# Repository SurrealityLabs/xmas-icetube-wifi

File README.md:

# xmas-icetube-wifi
Wifi adapter for the xmas-icetube clock PCB

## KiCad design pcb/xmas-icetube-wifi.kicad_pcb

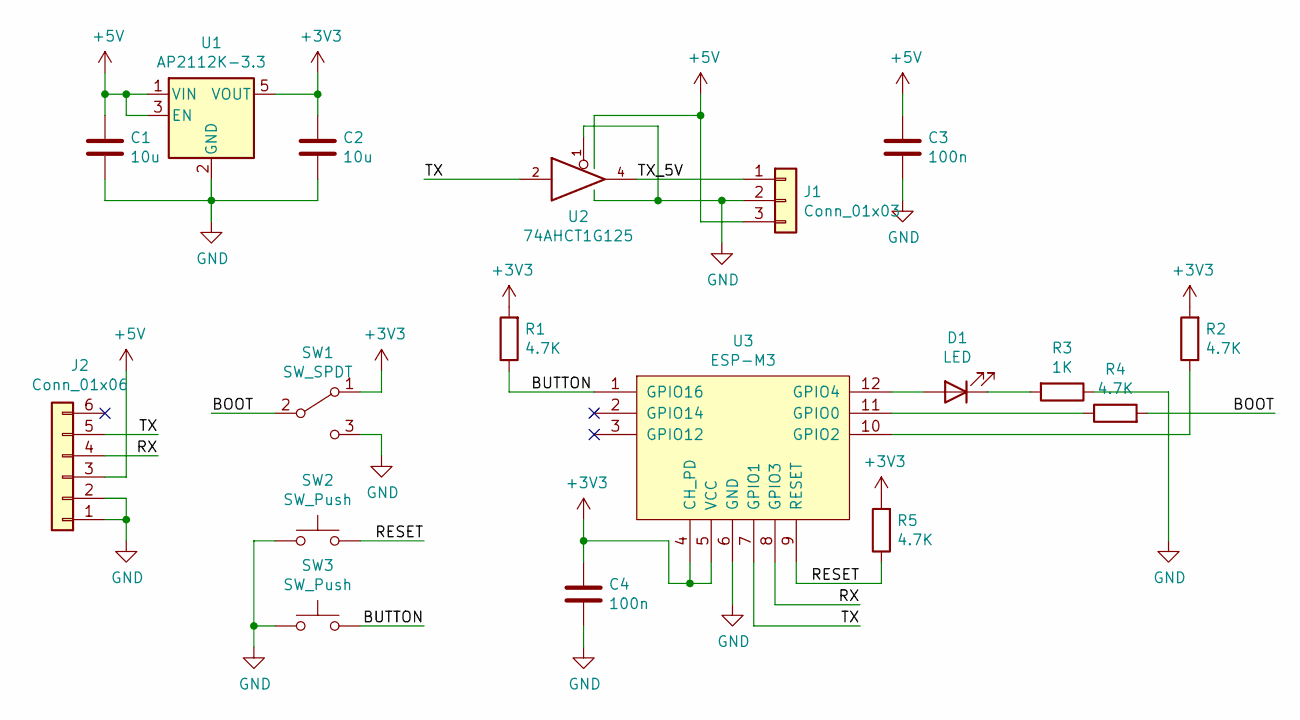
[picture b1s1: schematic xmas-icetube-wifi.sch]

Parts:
C1, C2: 10u; C_0805_2012Metric
C3, C4: 100n; C_0603_1608Metric
D1: LED; LED_0603_1608Metric
J1: Conn_01x03; PinSocket_1x03_P2.54mm_Vertical
J2: Conn_01x06; PinHeader_1x06_P2.54mm_Horizontal
R1, R2, R4, R5: 4.7K; R_0603_1608Metric
R3: 1K; R_0603_1608Metric
SW1: SW_SPDT; SW_SPDT_PCM12
SW2, SW3: SW_Push; SW_SPST_PTS810
U1: AP2112K-3.3; SOT-23-5
U2: 74AHCT1G125; SOT-23-5
U3: ESP-M3

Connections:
+3V3: C2.1, C4.1, R1.2, R2.2, R5.2, SW1.1 (A), U1.5 (VOUT), U3.4 (CH_PD), U3.5 (VCC)
+5V: C1.1, C3.1, J1.3, J2.3, U1.1 (VIN), U1.3 (EN), U2.5 (VCC)
/BOOT: R4.2, SW1.2 (B)
/BUTTON: R1.1, SW3.2, U3.1 (GPIO16)
/RESET: R5.1, SW2.2, U3.9 (RESET)
/RX: J2.4, U3.8 (GPIO3)
/TX: J2.5, U2.2, U3.7 (GPIO1)
/TX_5V: J1.1, U2.4
GND: C1.2, C2.2, C3.2, C4.2, J1.2, J2.1, J2.2, R3.1, SW1.3 (C), SW2.1, SW3.1, U1.2 (GND), U2.1, U2.3 (GND), U3.6 (GND)
unnamed: D1.1 (K), R3.2
unnamed: D1.2 (A), U3.12 (GPIO4)
unnamed: R2.1, U3.10 (GPIO2)
unnamed: R4.1, U3.11 (GPIO0)

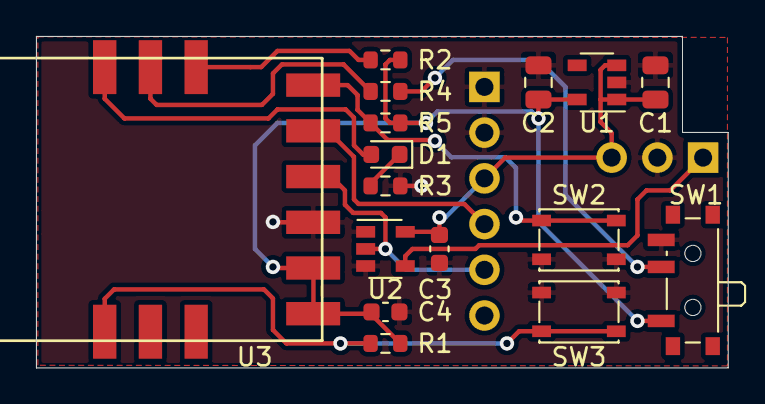
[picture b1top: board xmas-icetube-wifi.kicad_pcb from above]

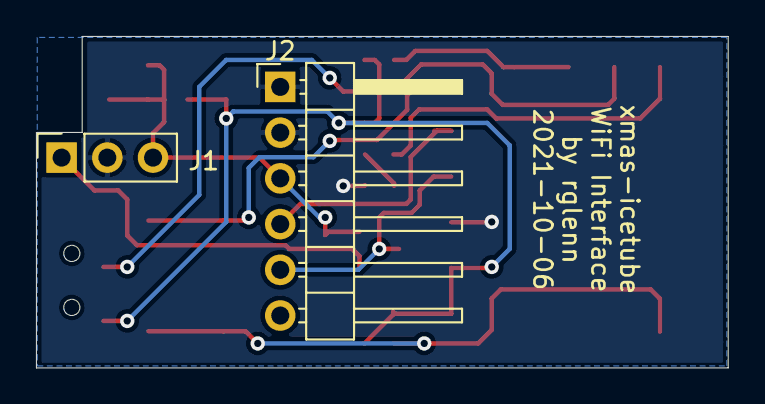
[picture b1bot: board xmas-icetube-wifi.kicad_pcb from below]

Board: 2 copper layers, 38.4 x 18.4 mm, 18 parts (2 on the bottom side), 13 nets.

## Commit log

2021-11-01 Adding PCB files
2021-11-01 Updating PCB with longer ESP-M3 footprint
